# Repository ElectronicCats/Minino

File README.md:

# Minino

<p align="center">
    
</p>

<p align=center>

</p>

Minino is an original multiprotocol and multiband board made for sniffing, communicating, and attacking IoT (Internet of Things) devices. It was designed as a mini Cat that integrates the powerful ESP32-C6, GPS, microSD card slot, and OLED display. This board is a mini Swiss army knife for IoT security researchers, developers, and enthusiasts. 

Minino can operate across multiple wireless technologies and RF tools:
- **BLE** (Trackers scanner for AirTag, SmartTag, Tile, Chipolo & BLE Spam / HID)
- **Wi-Fi** (Sniffer, Deauthenticator, CatDoS, SSID Spam, Captive Portal, DroneID)
- **RF Spectrum Analyzer** (2.4 GHz Wi-Fi & Zigbee real-time analyzer, Fox Hunting, Peak Tracker, Jammer & DroneID IDS, PCAP capture)
- **Software Defined Radio (SDR)** (Native 80 MS/s I/Q transceiver, CW/Packet TX, On-Chip FFT, and [ESPARGOS WebSDR](https://espargos.net/espsdr/app/) Host)
- **Surveillance Detection** (Flock Safety ALPR, Body Cams, Skimmers)
- **Zigbee** (IEEE 802.15.4 Sniffer over CLI and Spoofing)
- **Thread & Matter** (IEEE 802.15.4 / 6LoWPAN Sniffer and Broadcast)
- **GPS** (Wardriving & Geotagged Evidence Logging)

## Features
- Compatible with CatSniffer's PyCatSniffer
- Compatible with Wireshark (Live serial streaming & `.pcap` logging on microSD)
- Compatible with [ESPARGOS WebSDR](https://espargos.net/espsdr/app/) (Browser-based real-time waterfall, FFT spectrum, and I/Q capture over WebSerial)
- Real-time 2.4 GHz RF Spectrum Analyzer with Fox Hunting, 2X Peak Tracker, EMA filtering, and Smart Anti-Jammer detection
- Selectable OLED Menu Styles (`Classic`, `Icon List`, `Grid`, `Hero + Dock`)
- WarDriving (WiFi, Zigbee, Thread, BLE, Surveillance)
- Multiprotocol packet sniffing
- Supports `.pcap` and `.iq` file storage on microSD
- File Manager Web & Local OLED Browser
- Unified firmware image generation (`minino-merged.bin` and `minino-merged.hex`)
- OpenSource & Open Hardware
- OTA Updates

### TODO Features

`[] Features coming soon [x] Working features`

>[!IMPORTANT]
> OTA requires 8MB. If you want to build for other memory capacities, compile without OTA.

### Menu: Applications (`Applications`)

#### WiFi (`Applications > WiFi`)
- [x] **Wardriving**: Geotagged WiFi AP discovery with GPS coordinates.
- [x] **WiFi Sniffer / Analyzer**: Real-time 2.4 GHz channel traffic monitoring and AP summary.
- [x] **WiFi Deauther**: Injects 802.11 deauthentication frames to disconnect target devices.
- [x] **Deauth Scan (Detector)**: Continuously monitors the airwaves for active deauth attacks.
- [x] **DOS Attack (CatDoS)**: Wireless Denial of Service and beacon flooding.
- [x] **SSID Spammer**: Broadcasts thousands of fake WiFi Access Points simultaneously.
- [x] **Captive Portal**: Rogue AP with captive portal web server for testing.
- [x] **DroneID Scanner**: Listens for and decodes ASTM F3411 Remote ID drone telemetry and GPS location.
- [x] **DroneID Transmitter**: Broadcasts simulated Drone Remote ID beacons.
- [x] **Modbus TCP**: Industrial IoT and SCADA Modbus TCP endpoint scanner.
- [x] **Flock / ALPR Detector**: Detects Flock Safety ALPR cameras, body cams, and skimmers.
- [x] **Flock Simulator**: Transmits test surveillance telemetry beacons for detection auditing.
- [ ] Wireshark integration

#### BLE (`Applications > Bluetooth`)
- [x] **BLE Spammer**: Floods advertisement popups targeting iOS (Apple), Android, Windows, and Samsung devices.
- [x] **BLE Saturate**: Lab-only channel-saturation mode with 20 ms advertising and MAC rotation.
- [x] **BLE Matter Spoof**: Emits Matter commissioning onboarding advertisements (`0xFFF6`).
- [x] **BLE HID Spoofing**: Emulates Bluetooth Human Interface Devices (keyboard, mouse, media remote).
- [x] **BLE ADV Sniffer**: Raw advertisement packet sniffer with Wireshark serial streaming.
- [x] **BLE Trackers Scanner**: Detects and tracks Apple AirTags, Samsung SmartTags, Tile, and Chipolo with RSSI signal and distance estimation.
- [x] **Wireshark integration**: Real-time BLE packet capture over serial.

#### Zigbee (`Applications > Zigbee`)
- [x] **Zigbee Sniffer**: IEEE 802.15.4 over-the-air packet sniffer.
- [x] **Zigbee Spoofing**: End Device emulation (smart light bulbs and switches).
- [x] **Mesh Topology**: Passive PAN/link map with LQI/RSSI and SD logging.
- [x] **Wardriving (WarBee)**: Geotagged Zigbee network reconnaissance with channel hopping.
- [x] **Wireshark integration**: Zigbee frame capture streaming to Wireshark.

#### Thread (`Applications > Thread`)
- [x] **Thread Sniffer**: IEEE 802.15.4 / 6LoWPAN Thread network packet sniffer.
- [x] **Thread Broadcast**: Injects multicast and broadcast packets into Thread networks.
- [x] **Wardriving (WarThread)**: Geotagged Thread/802.15.4 reconnaissance with MLE parsing.
- [x] Wireshark integration

#### Matter (`Applications > Matter`)
- [x] **Matter onboarding advertisement spoofing (BLE)**: `Applications > Bluetooth > Spam > Matter`.
- [ ] Matter protocol support
- [ ] Matter CLI

#### GPS (`Applications > GPS`)
- [x] **Wardriving**: Geotagged reconnaissance (WiFi, Zigbee, Thread) logged to SD card.
- [x] **Location**: Displays real-time latitude, longitude, and altitude coordinates.
- [x] **Speed**: Displays GPS ground speed (km/h) and heading direction.
- [x] **Date & Time**: Atomic clock synchronization and RTC update.
- [x] **Route**: Route and waypoint recording to SD card (.gpx / .csv).
- [x] **Num Sats**: Displays active satellite constellation and SNR signal quality.
- [ ] GPS Sleep

#### GPIO (`Applications > GPIO`)
- [x] **I2C Scanner**: Scans external I2C bus (SDA/SCL) device addresses.
- [x] **UART Bridge**: Hardware serial bridge / pass-through console on UART2.

#### File Manager (`Applications > File Manager`)
- [x] **File Manager Local**: On-device microSD file browser using OLED screen and buttons.
- [x] **File Manager Web**: Embedded HTTP web server for WiFi-based file downloads and uploads.

#### Spectrum (`Applications > Spectrum`)
- [x] **14-Channel Bars (`BARS`)**: Real-time 2.4 GHz bar chart overview with Peak Hold markers across all channels.
- [x] **Live Channel Scope (`SCOPE`)**: Single-channel rolling time-domain power curve and RSSI telemetry.
- [x] **2D Waterfall (`WATER`)**: Rolling spectrogram for visualizing transient transmissions and duty cycles.
- [x] **Fox Hunting Meter (`FOX`)**: High-contrast direction-finding proximity gauge (`0-100%`), calibrated dBm scale (`-90` to `-30 dBm`), Peak Hold line, and Squelch threshold marker.
- [x] **2X Peak Tracker (`PEAK`)**: Big-font display highlighting the strongest active signal (`dBm`), channel number, and center frequency (`MHz`) for rapid field readings.
- [x] **Dual-Band & Tri-Channel Sweep**: Supports both **Wi-Fi** (`Ch 1-14`, `2412-2484 MHz`) and **IEEE 802.15.4 / Zigbee** (`Ch 11-26`, `2405-2480 MHz`), plus rapid **Tri-Channel Sweep** (`Ch 1, 6, 11`).
- [x] **Smart Anti-Jammer & RF IDS**: Multi-factor evaluator (`rf_jammer_evaluate`) and EMA filter (`rf_filter_ema_rssi`) that distinguish Layer-1 RF noise/CW jammers and Layer-2 Deauth floods (`0xC0`/`0xA0`) from normal high-throughput AP traffic and adjacent-channel spillover.
- [x] **Passive DroneID Detection**: Inspects ASTM F3411 (`OUI FA:0B:BC`), French Direct Remote ID (`OUI 6A:5C:35`), and Wi-Fi Aware NAN (`88:69:19:9D:92:09`) frames to alert and log active drone UAS IDs per channel.
- [x] **Direct PCAP & CSV Logging**: Streams raw 802.11 frames to microSD (`/sdcard/spectrum_XX.pcap`) and signal telemetry to CSV without dropping the spectrum view.

#### SDR (`Applications > SDR`)
- [x] **RX I/Q Burst Capture (`[IDL]` / `[RX]`)**: Native in-process 80 MS/s hardware DMA/dump capture into reserved SRAM (`0x40840000`), live physical RSSI calculation (`dBm`), and automatic `.iq` file saving to microSD (`/sdcard/sdrcapXX.iq`).
- [x] **802.11 Raw Packet TX (`[TX:PKT]`)**: Injects bursts of custom 802.11 raw Probe Request frames (`MININO-SDR-TX`) on the selected channel (`2412-2484 MHz`, `Ch 1-14`).
- [x] **PHY Continuous Wave Carrier (`[TX:CW]`)**: Emits an unmodulated RF test carrier on the tuned frequency via the ESP32-C6 PHY synthesizer with a 30-second hardware safety timeout.
- [x] **ESPARGOS WebSDR Host (`[HOST]`)**: Streams real-time I/Q bursts (`CAP16`/`CAP20` at `80`, `40`, or `16 MS/s` with software decimation and LNA gain control `0-60 dB`) and on-chip radix-2 FFT spectrum frames (`SPEC` / `SPC1`) over USB directly to the **[ESPARGOS WebSDR App (`https://espargos.net/espsdr/app/`)](https://espargos.net/espsdr/app/)**.

---

### Menu: Settings (`Settings`)
- [x] **Display**: Configures OLED screensaver style and timeout.
- [x] **Menu Style**: Selectable OLED menu rendering views persisted in NVS (**Classic**, **Icon List**, **Grid**, and **Hero + Dock**).
- [x] **Logs Output**: Configures serial and on-screen log levels.
- [x] **SD Card Settings**: Displays SD capacity, checks format integrity, and provides FAT32 formatting.
- [x] **WiFi Settings**: Manages WiFi station credentials and radio settings.
- [x] **Stealth Mode**: Disables all LEDs, buzzer sounds, and screen animations for silent operation.
- [x] **Light Sleep Mode**: Low-power sleep mode for battery saving.
- [ ] Deep Sleep Mode

---

### Menu: About (`About`)
- [x] **Version & License**: Displays firmware version, build date, and licensing details.
- [x] **Credits & Legal**: Contributor credits and responsible disclosure notice.
- [x] **OTA Firmware Update**: Over-The-Air firmware updates via WiFi.

---

## Firmware profiles and memory budget

The default firmware includes the **Zigbee/OpenThread stacks**, so their apps
are native entries in `Applications`:

```bash
cd firmware
make compile                 # default: BLE/WiFi + Zigbee/Thread
make build-sdr               # SDR capture bank, Zigbee/Thread off
```

The SDR variant turns the stacks off because the capture bank needs the SRAM.
In the default combined build, `bt_spam` starts with roughly 20 KB free after
Bluedroid comes up and refuses to advertise below **18 KB**; it stops the loop
below **8 KB**. This prevents `btm_ble_write_adv_enable_complete failed` after
using Thread Sniffer/Broadcast, when the heap is lower.

---

## Native 80 MS/s SDR Transceiver & ESPARGOS WebSDR Host

Minino integrates a **native, in-process Software Defined Radio (SDR)** engine (`firmware/main/modules/esp_sdr/`) running directly inside Minino OS without requiring dual-boot or a secondary `ota_1` partition. It drives the ESP32-C6 hardware I/Q dump engine at **80 MS/s**, reserves the 128 KiB SRAM Block 2 (`0x40840000 - 0x40860000`) at link time (`esp_sdr_bank.ld`), and locks the USB-Serial-JTAG reset register (`usb_uart_chip_rst_dis = 1`) while active so browser WebSerial DTR/RTS transitions never reboot the board.

### Building & Flashing the SDR Firmware Variant
Because the hardware I/Q capture bank requires 128 KiB of contiguous SRAM below `0x40840000`, the SDR variant compiles without the Zigbee and OpenThread stacks to fit within the 256 KiB lower-SRAM budget (`profiles/sdr/profile`). Every build automatically generates both individual partition binaries and unified single-file images (`minino-merged.bin` and `minino-merged.hex`):

```bash
cd firmware
make build-sdr                                    # Builds the SDR-enabled firmware in build-sdr/
idf.py -B build-sdr -p /dev/ttyACM0 flash         # Flashes bootloader, partition table, and app
```

Or flash the single unified binary at address `0x0`:
```bash
esptool.py --chip esp32c6 -p /dev/ttyACM0 write_flash 0x0 build-sdr/minino-merged.bin
```

### The 4 Operating Modes on Device (`Applications > SDR`)
Inside `Applications > SDR` (or by running `sdr_capture` in the serial console), press **`BOOT`** or **hold `RIGHT`** to cycle through the four operating modes:

| Mode Header | Function | Controls |
| :--- | :--- | :--- |
| **`MININO SDR [IDL]` / `[RX]`** | **RX I/Q Burst Capture**: Captures 8,192 32-bit I/Q words (`10-bit signed I` in bits `9:0`, `10-bit signed Q` in bits `19:10`) at 80 MS/s, computes physical RSSI (`dBm`), and saves `/sdcard/sdrcapXX.iq`. | `UP`/`DOWN`: Tune `2412-2484 MHz` (`Ch 1-14`)<br>`RIGHT`: Capture & Save<br>`BOOT` / `Hold RIGHT`: Next mode<br>`LEFT`: Exit |
| **`MININO SDR [TX:PKT]`** | **802.11 Raw Packet Injection**: Transmits 5-packet bursts of raw 802.11 Probe Request frames (`SSID: MININO-SDR-TX`) on the active channel. | `UP`/`DOWN`: Tune channel<br>`RIGHT`: Send packet burst<br>`BOOT` / `Hold RIGHT`: Next mode |
| **`MININO SDR [TX:CW]`** | **PHY Continuous Wave Tone**: Emits an unmodulated RF carrier via the ESP32-C6 PHY synthesizer (`c6_sdr_tx_carrier_start`) with an automatic **30-second safety timeout**. | `UP`/`DOWN`: Tune channel<br>`RIGHT`: Toggle CW ON/OFF<br>`BOOT` / `Hold RIGHT`: Next mode |
| **`MININO SDR [HOST]`** | **ESPARGOS WebSDR Host**: Serves the ESP-SDR line/binary protocol over USB for real-time waterfall, FFT, and I/Q streaming in the browser. | `BOOT`: Exit Host mode to RX<br>`LEFT`: Stop Host & Exit app |

### Using the SDR Host with the ESPARGOS WebSDR Page
Minino is fully compatible with the official **[ESPARGOS WebSDR application (`https://espargos.net/espsdr/app/`)](https://espargos.net/espsdr/app/)**, providing a real-time waterfall, spectrum analyzer, constellation viewer, and I/Q burst streamer in any Chromium-based browser (Chrome, Edge, Brave) via WebSerial:

1. **Connect Minino via USB** and open `Applications > SDR` on the device.
2. **Open [https://espargos.net/espsdr/app/](https://espargos.net/espsdr/app/)** in your browser and click **Connect** to select the Minino USB serial port (`/dev/ttyACM0` or `COMx`).
3. **Automatic & Manual Activation**:
   - **Auto-Switch from SDR App**: If you are anywhere inside `Applications > SDR`, as soon as the ESPARGOS web app sends its initial `SYNC` handshake, Minino **automatically switches into `[HOST]` mode**, suspends the interactive serial console, and begins streaming.
   - **Manual Toggle on OLED**: Press `BOOT` (or hold `RIGHT`) inside the SDR app until the screen displays `MININO SDR [HOST]` (`Web: espargos.net` / `App: /espsdr/app`), then click **Connect** on the web page.
   - **From Serial Console**: Type `sdr_host` in the Minino console (`115200` baud) to hand over the USB port directly.
4. **Supported ESPARGOS WebSDR Capabilities**:
   - **On-Chip Spectrum (`SPEC` / `SPC1`)**: High-FPS radix-2 Q15 FFT computed directly on the ESP32-C6 (`256`, `512`, `1024`, or `2048` bins) with DC offset modes (`DC 0`/`DC 1`) and zlib CRC32 verification.
   - **Raw I/Q Burst Streaming (`CAP16` / `CAP20`)**: 8-bit (`CAP16`) and 10-bit packed (`CAP20`) I/Q transfers with hardware-chunked 64-byte USB FIFO writes.
   - **Live Parameter Negotiation**: Supports on-the-fly center frequency tuning (`FREQ 2412..2484`), sample rate decimation (`80 MS/s`, `40 MS/s`, `16 MS/s`), and RX LNA gain control (`GAIN 0..60 dB`).
5. **Exiting Host Mode**: Disconnect from the browser (sends `RELEASE`), press `LEFT` or `BOOT` on Minino, or send `MININO\n` over serial. *(Note: Do not click "Flash Firmware..." on the ESPARGOS page, as that overwrites Minino OS with upstream esp-sdr).*

---

## RF Spectrum Analyzer & Fox Hunting

The **RF Spectrum Analyzer** (`Applications > Spectrum`, implemented in `firmware/main/apps/rf_spectrum/`) operates directly on the ESP32-C6 physical (PHY) and MAC layers to provide real-time 2.4 GHz situational awareness and transmitter hunting:

- **5 Interactive OLED Views** (cycle with `RIGHT`):
  1. **`BARS`**: 14-channel bar chart with Peak Hold indicators.
  2. **`SCOPE`**: Single-channel real-time RSSI oscilloscope trace.
  3. **`WATER`**: 2D rolling waterfall spectrogram.
  4. **`FOX` (Fox Hunting)**: High-contrast direction-finding proximity meter (`0-100%`) with calibrated dBm ticks (`-90` to `-30 dBm`), Peak Hold line (`|`), Squelch marker (`:`), and Geiger counter audio clicks (`HOLD UP`).
  5. **`PEAK` (2X Peak Tracker)**: Large 2X-scaled readout of the strongest detected signal (`dBm`), channel, and frequency (`MHz`).
- **Signal Processing & Smart Anti-Jammer**:
  - **EMA Smoothing**: Applies an Exponential Moving Average filter (`rf_filter_ema_rssi`) to stabilize noisy RSSI readings while preserving rapid peak attack.
  - **Intelligent Jammer Evaluator (`rf_jammer_evaluate`)**: Cross-checks RSSI saturation (`>= -45 dBm`), valid 802.11 frame counts, beacon presence, FCS CRC error ratios, Deauth/Disassoc counts (`0xC0`/`0xA0`), and adjacent-channel AP spillover (`+-1` channel at `>= -38 dBm`) to eliminate false positives from nearby routers.
- **Passive DroneID & PCAP Forensics**:
  - Automatically decodes ASTM F3411 / ASD-STAN (`FA:0B:BC`), French Direct Remote ID (`6A:5C:35`), and Wi-Fi Aware NAN (`88:69:19:9D:92:09`) beacons, displaying `! DRONE CH X !` and logging the drone's serial `UAS ID`.
  - Hold `DOWN` (or run `spectrum_pcap on`) to stream raw 802.11 frames into sequential `/sdcard/spectrum_00.pcap` files compatible with Wireshark.
- **Serial Console Commands**: Control and inspect live state via `spectrum_pcap [on|off|toggle]`, `spectrum_drone [clear]`, `spectrum_ids [clear]`, `threshold [<dBm>|off]`, `spectrum_audio [on|off|toggle]`, `spectrum_band [wifi|zigbee]`, and `exit_app`.

---

## Core Architecture & Resource Arbitration

Minino OS uses a deterministic resource management and lifecycle architecture across all wireless modules:
- **`radio_lease` (`components/radio_lease/`)**: Reference-counted hardware arbiter that manages mutually exclusive Wi-Fi/802.15.4 and BLE radio claims plus shared promiscuous RX leases (`RADIO_PROM_SDR_RX`, `RADIO_PROM_SPECTRUM`, `RADIO_PROM_SURV`, `RADIO_PROM_ANALYZER`).
- **`wifi_service` (`components/wifi_service/`)**: Centralizes `esp_wifi_init()` and netif creation so switching between AP, STA, Sniffer, Spammer, and SDR modes never triggers duplicate netif assertions or memory leaks.
- **`gap_dispatcher` & `gatt_dispatcher` (`components/gap_dispatcher/`)**: Multiplexes Bluedroid GAP and GATTC callbacks to multiple concurrent subscribers without callback rotation conflicts.
- **`app_manager` & Selectable OLED Menu Styles (`main/modules/menus_module/`)**: Clean `minino_app_t` (`on_enter`, `on_input`, `on_exit`) lifecycle with a dedicated FreeRTOS button input queue and four NVS-persisted UI styles (`Classic`, `Icon List`, `Grid`, `Hero + Dock`).
- **Host Unit Test Suite**: Over 20 host-side Unity and Python test suites (`make -C firmware tests`) validating protocol parsers, FFT math, channel clamping, radio leases, and NMEA/PCAP formatting on standard `gcc` without hardware.

---

## BLE Trackers Scanner
Minino includes a dedicated scanner and tracker for Bluetooth Low Energy beacon devices:
- **Supported Ecosystems**: Apple Find My / AirTags, Samsung Galaxy SmartTag / SmartTag2, Tile (Mate, Pro, Slim), and Chipolo.
- **Proximity & Signal Monitoring**: Real-time RSSI signal tracking, proximity approximation, and packet reception rates.
- **Detailed Inspection**: Live viewing of device MAC address, manufacturer payload, registered status, and last-seen timestamps.
- **Paging & Filtering**: Navigate easily across multiple active trackers in range.

## Surveillance & Flock Safety Detector
Minino features an advanced passive detection engine designed to detect physical surveillance infrastructure in real time:
- **Flock Safety / ALPR Detection**: Detects Automated License Plate Readers (ALPR) such as Flock Safety cameras, Falcon systems, and Raven audio detection units.
- **Multi-Vector Fingerprinting**:
  - **WiFi**: Matches known OUI vendor prefixes (35+ Flock OUIs, DeFlock database), surveillance SSIDs (`flocksafety`, `pigvision`, `fs ext`, `penguin`, etc.), and 802.11 Information Element (IE) signatures.
  - **BLE**: Identifies characteristic advertising beacons and vendor payloads (e.g. Xuntong BLE modules, Flock battery diagnostics).
- **Body Cameras & Skimmers**: Identifies Axon Body Worn Cameras and common Bluetooth-based payment skimmers.
- **Evidence Capture & GPS**: Automatically stores detected devices with GPS coordinates (`.csv` / `.gpx`) and captures raw network traffic (`.pcap`) on the microSD card.

Inspired by projects such as [Amini Project](https://github.com/Ocelot-Offensive-Security/Arsenal) and [USBNugget](https://github.com/HakCat-Tech/USB-Nugget).

## How to build the firmware

Check the [Developer guide](./firmware/README.md) to learn how to build the firmware from scratch.

## How to contribute 

Contributions are welcome!

Please read the document [**Contribution manual**](https://github.com/ElectronicCats/electroniccats-cla/blob/main/electroniccats-contribution-manual.md) which will show you how to contribute your changes to the project.

✨ Thanks to all our [Contributors](https://github.com/ElectronicCats/Minino/graphs/contributors)! ✨

See [**_Electronic Cats CLA_**](https://github.com/ElectronicCats/electroniccats-cla/blob/main/electroniccats-cla.md) for more information.

See the [**Community code of conduct**](https://github.com/ElectronicCats/electroniccats-cla/blob/main/electroniccats-community-code-of-conduct.md) for a vision of the community we want to build and what we expect from it.

## License

Electronic Cats invests time and resources providing this open source design, please support Electronic Cats and open-source hardware by purchasing products from Electronic Cats!

Designed by Electronic Cats.

Firmware released under a GNU AGPL v3.0 license. See the LICENSE file for more information.

Hardware released under a CERN Open Hardware Licence v1.2. See the LICENSE_HARDWARE file for more information.

Electronic Cats is a registered trademark, please do not use if you sell these PCBs.

Nov 29 2022

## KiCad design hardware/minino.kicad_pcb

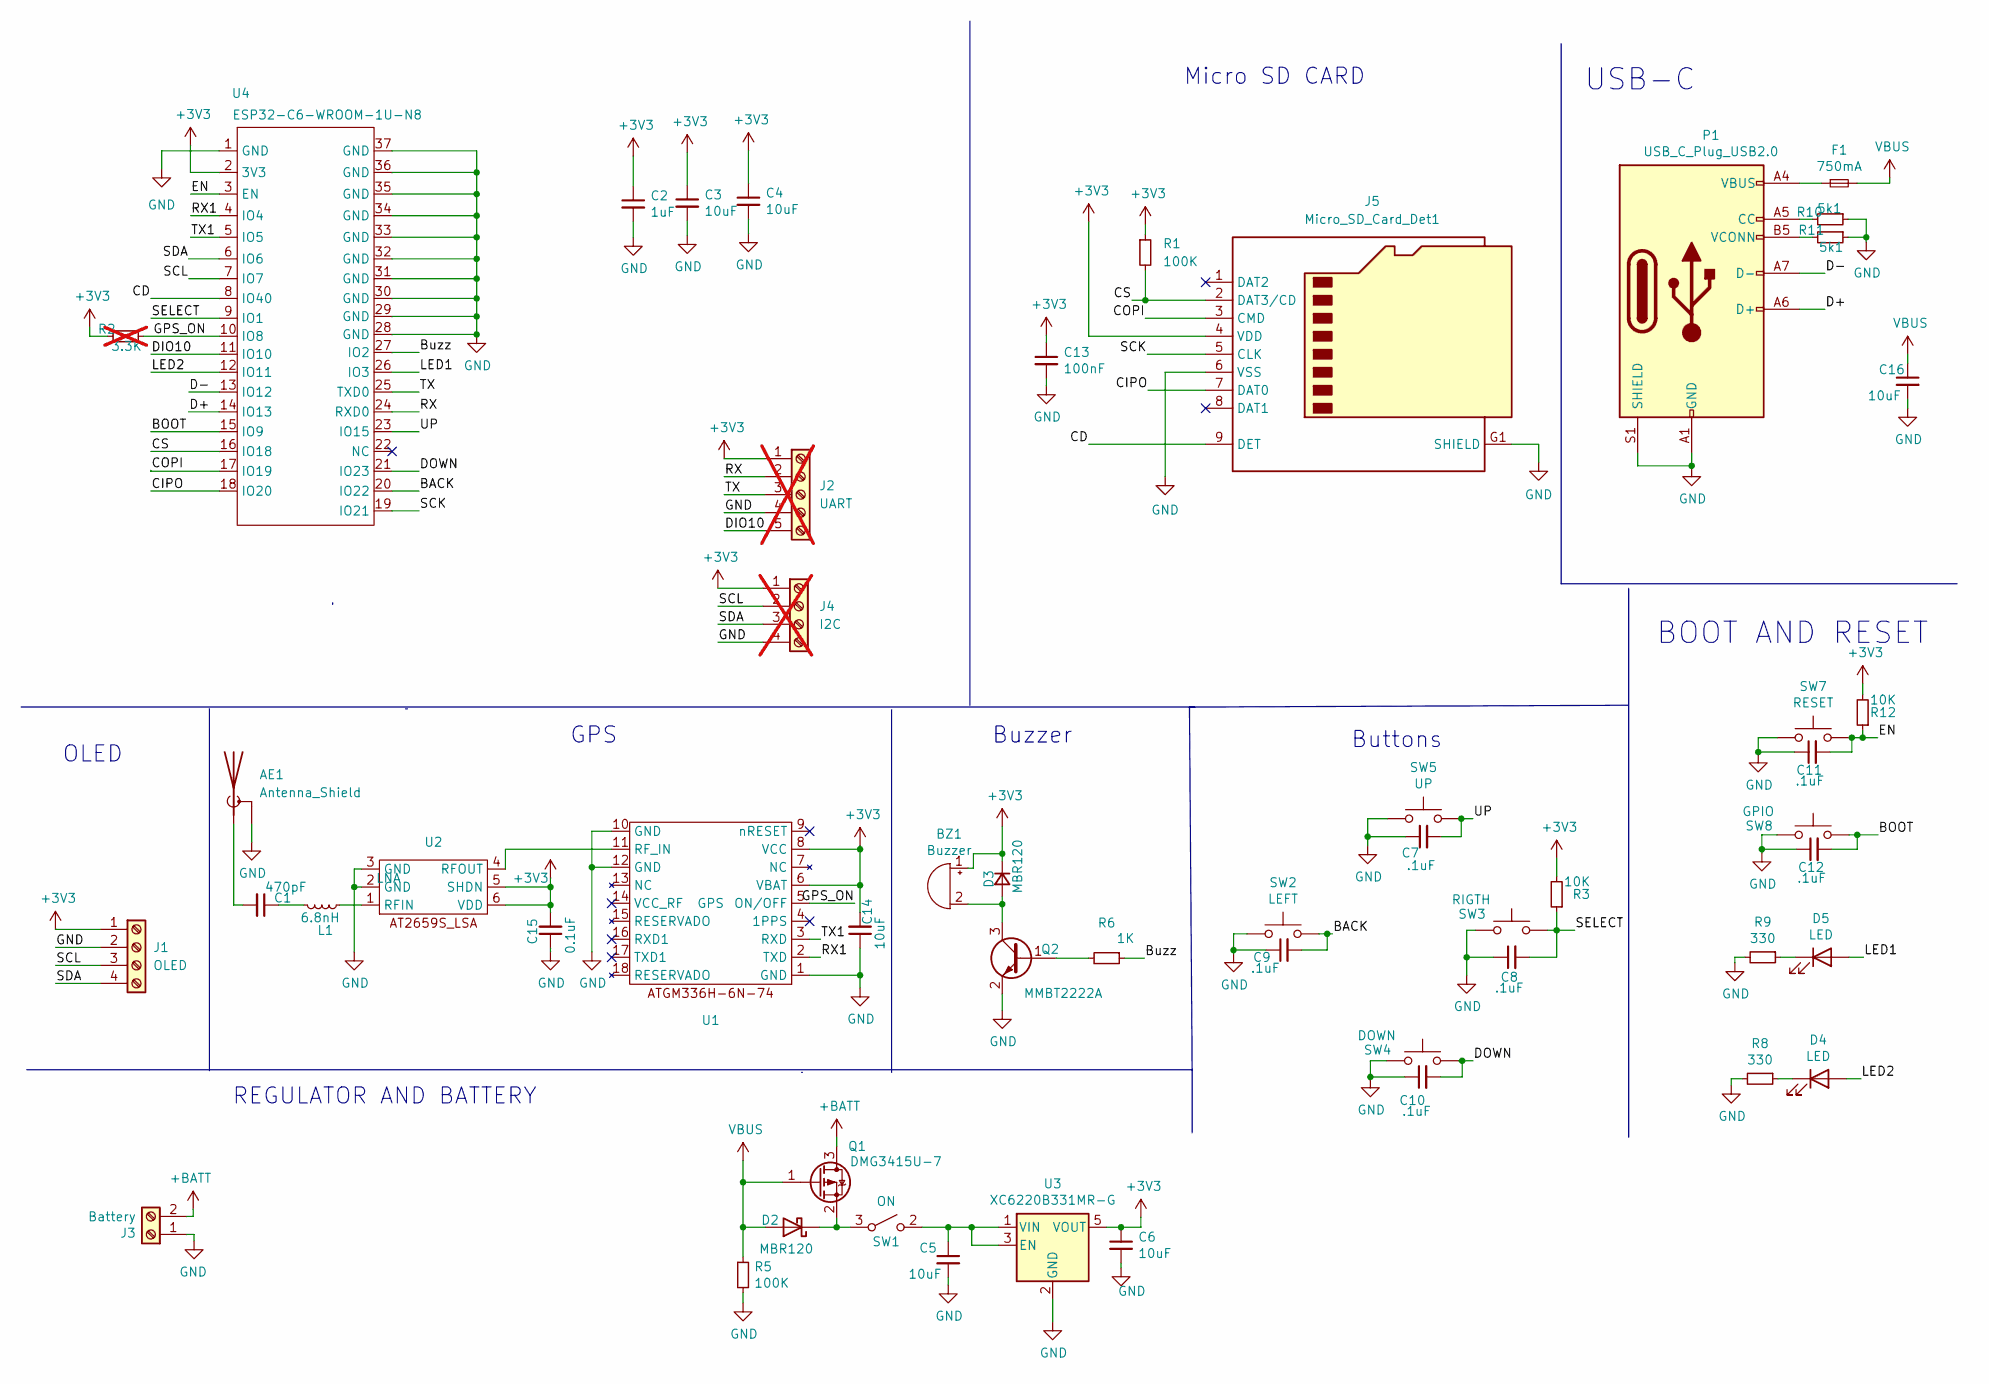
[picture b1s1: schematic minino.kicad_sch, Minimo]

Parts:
AE1: Antenna_Shield; U.FL_Molex_MCRF_73412-0110_Vertical; LCSC# C7426714
BZ1: Buzzer; Buzzer4x4; LCSC# C556936
C1: 470pF; C_0603_1608Metric; LCSC# C1620
C2: 1uF; C_0603_1608Metric; LCSC# C15849
C3, C4, C5, C6, C14, C16: 10uF; C_0603_1608Metric; LCSC# C85713
C7, C8, C9, C10, C11, C12: .1uF; C_0603_1608Metric; LCSC# C478888
C13: 100nF; C_0603_1608Metric; LCSC# C149620
C15: 0.1uF; C_0603_1608Metric; LCSC# C478888
D2, D3: MBR120; D_SOD-123F; LCSC# C130880
D4, D5: LED; LED_0805_2012Metric_Pad1.15x1.40mm_HandSolder; LCSC# C965815
F1: 750mA; Fuse_0603_1608Metric; LCSC# C182438
J1: OLED; PinHeader_1x04_P2.54mm_Vertical
J2: UART; PinHeader_1x05_P2.54mm_Vertical; LCSC# C492404; not fitted
J3: Battery; BAT-TH_BH-AAA-A1AJ024; LCSC# C5290193
J4: I2C; PinHeader_1x04_P2.54mm_Vertical; LCSC# C2691448; not fitted
J5: Micro_SD_Card_Det1; SUNTECH_ST-TF-003A; LCSC# C393941
L1: 6.8nH; L_0603_1608Metric_Pad1.05x0.95mm_HandSolder; LCSC# C49447
P1: USB_C_Plug_USB2.0; C393939; LCSC# C393939
Q1: DMG3415U-7; SOT-23; LCSC# C96616
Q2: MMBT2222A; SOT-23; LCSC# C181121
R1, R5: 100K; R_0603_1608Metric; LCSC# C25803
R2: 3.3K; R_0603_1608Metric; LCSC# C403480; not fitted
R3, R12: 10K; R_0603_1608Metric; LCSC# C217281
R6: 1K; R_0603_1608Metric_Pad0.98x0.95mm_HandSolder; LCSC# C110776
R8, R9: 330; R_0603_1608Metric; LCSC# C25231
R10, R11: 5k1; R_0603_1608Metric; LCSC# C191782
SW1: ON; JS102011SAQN; LCSC# C221660
SW2: LEFT; SW_SPST_TL3342; LCSC# C318889
SW3: RIGTH; SW_SPST_TL3342; LCSC# C318889
SW4: DOWN; SW_SPST_TL3342; LCSC# C318889
SW5: UP; SW_SPST_TL3342; LCSC# C318889
SW7: RESET; SW_SPST_TL3342; LCSC# C318889
SW8: GPIO; SW_SPST_TL3342; LCSC# C318889
U1: GPS; GPSM-SMD_ATGM336H; LCSC# C5804601
U2: LNA; AT2659S-LSA; LCSC# C883443
U3: XC6220B331MR-G; SOT-23-5; LCSC# C86534
U4: ESP32-C6-WROOM-1U-N8; MOD28_ESP32-C6-WROOM-1U_EXP

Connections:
+3V3: BZ1.1 (-), C2.1, C3.1, C4.1, C6.1, C13.1, C14.2, C15.2, D3.1 (K), J1.1, J2.1, J4.1, J5.4 (VDD), R1.1, R2.2, R3.2, R12.2, U1.6 (VBAT), U1.8 (VCC), U2.5 (SHDN), U2.6 (VDD), U3.5 (VOUT), U4.2 (3V3)
+BATT: J3.2, Q1.3 (D)
/BACK: C9.2, SW2.2, U4.20 (IO22)
/BOOT: C12.2, SW8.2, U4.15 (IO9)
/Buzz: R6.1, U4.27 (IO2)
/CD: J5.9 (DET), U4.8 (IO40)
/CIPO: J5.7 (DAT0), U4.18 (IO20)
/COPI: J5.3 (CMD), U4.17 (IO19)
/CS: J5.2 (DAT3/CD), R1.2, U4.16 (IO18)
/D+: P1.A6 (D+), U4.14 (IO13)
/D-: P1.A7 (D-), U4.13 (IO12)
/DIO10: J2.5, U4.11 (IO10)
/DOWN: C10.2, SW4.2, U4.21 (IO23)
/EN: C11.2, R12.1, SW7.2, U4.3 (EN)
/GPS_ON: R2.1, U1.5 (ON/OFF), U4.10 (IO8)
/LED1: D5.2 (A), U4.26 (IO3)
/LED2: D4.2 (A), U4.12 (IO11)
/RX: J2.2, U4.24 (RXD0)
/RX1: U1.2 (TXD), U4.4 (IO4)
/SCK: J5.5 (CLK), U4.19 (IO21)
/SCL: J1.3, J4.2, U4.7 (IO7)
/SDA: J1.4, J4.3, U4.6 (IO6)
/SELECT: C8.2, R3.1, SW3.2, U4.9 (IO1)
/TX: J2.3, U4.25 (TXD0)
/TX1: U1.3 (RXD), U4.5 (IO5)
/UP: C7.2, SW5.2, U4.23 (IO15)
GND: AE1.2 (Shield), C2.2, C3.2, C4.2, C5.2, C6.2, C7.1, C8.1, C9.1, C10.1, C11.1, C12.1, C13.2, C14.1, C15.1, C16.2, J1.2, J2.4, J3.1, J4.4, J5.6 (VSS), J5.G1 (SHIELD), J5.G2 (SHIELD), J5.G3 (SHIELD), J5.G4 (SHIELD), P1.A1 (GND), P1.A12 (GND), P1.B1 (GND), P1.B12 (GND), P1.S1 (SHIELD), Q2.2 (E), R5.2, R8.2, R9.2, R10.1, R11.1, SW2.1, SW3.1, SW4.1, SW5.1, SW7.1, SW8.1, U1.1 (GND), U1.10 (GND), U1.12 (GND), U2.2 (GND), U2.3 (GND), U3.2 (GND), U4.1 (GND), U4.28 (GND), U4.29 (GND), U4.30 (GND), U4.31 (GND), U4.32 (GND), U4.33 (GND), U4.34 (GND), U4.35 (GND), U4.36 (GND), U4.37 (GND)
unnamed: AE1.1 (A), C1.2
unnamed: BZ1.2 (+), D3.2 (A), Q2.3 (C)
unnamed: C1.1, L1.2
unnamed: D2.1 (K), Q1.2 (S), SW1.3 (A)
unnamed: D4.1 (K), R8.1
unnamed: D5.1 (K), R9.1
unnamed: F1.1, P1.A4 (VBUS), P1.A9 (VBUS), P1.B4 (VBUS), P1.B9 (VBUS)
unnamed: P1.A5 (CC), R10.2
unnamed: P1.B5 (VCONN), R11.2
unnamed: Q2.1 (B), R6.2
unnamed: C5.1, SW1.2 (B), U3.1 (VIN), U3.3 (EN)
unnamed: U1.11 (RF_IN), U2.4 (RFOUT)
unnamed: L1.1, U2.1 (RFIN)
VBUS: C16.1, D2.2 (A), F1.2, Q1.1 (G), R5.1

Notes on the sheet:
REGULATOR AND BATTERY
Buzzer
Buttons
USB-C
OLED
BOOT AND RESET
Micro SD CARD
GPS

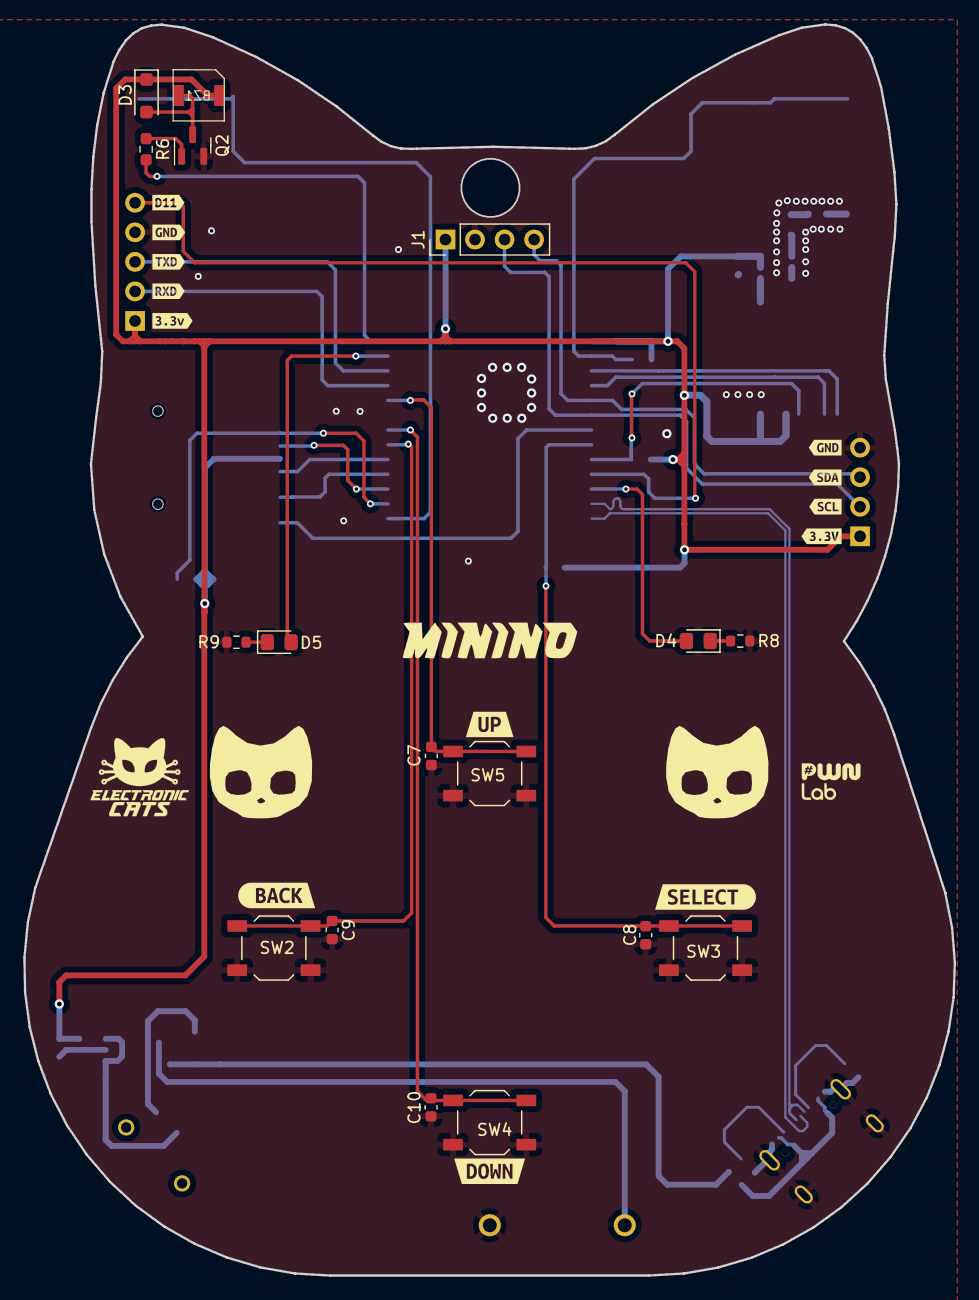
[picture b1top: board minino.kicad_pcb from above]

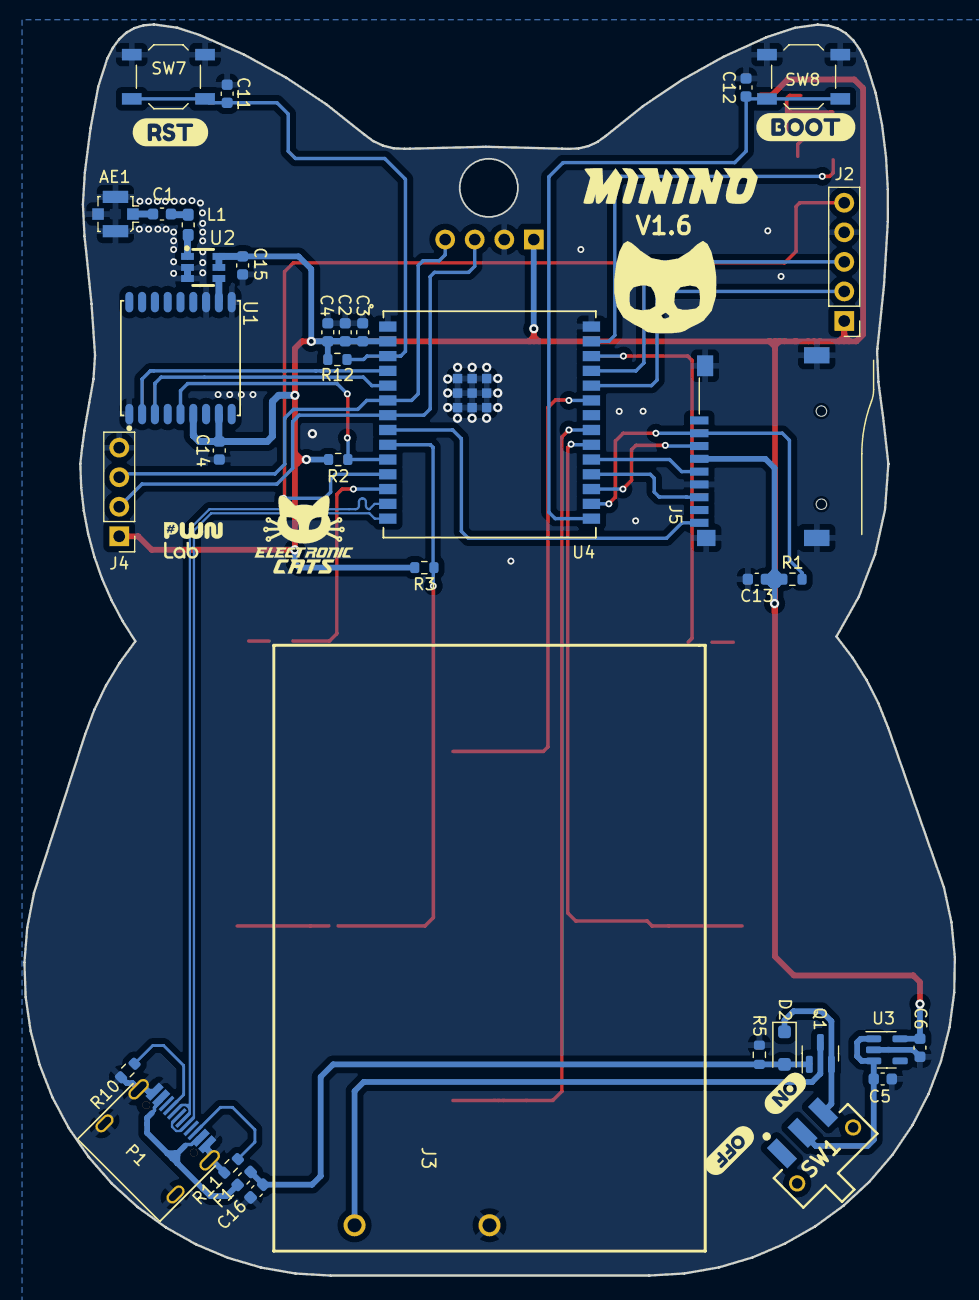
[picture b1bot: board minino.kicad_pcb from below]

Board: 2 copper layers, 80.0 x 107.5 mm, 70 parts (40 on the bottom side), 41 nets.

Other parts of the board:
kibuzzard-65BBE1AA: G***; kibuzzard-65BBE1AA
kibuzzard-65BBE1C5: G***; kibuzzard-65BBE1C5
kibuzzard-65BBE1CF: G***; kibuzzard-65BBE1CF
kibuzzard-65BBE26E: G***; kibuzzard-65BBE26E
kibuzzard-65BBE191: G***; kibuzzard-65BBE191
kibuzzard-65BBE243: G***; kibuzzard-65BBE243
kibuzzard-65BBE252: G***; kibuzzard-65BBE252
kibuzzard-65BBE261: G***; kibuzzard-65BBE261
kibuzzard-65BBE292: G***; kibuzzard-65BBE292
kibuzzard-65BC2D86: G***; kibuzzard-65BC2D86
kibuzzard-65BC2D94: G***; kibuzzard-65BC2D94
kibuzzard-65BC2DC7: G***; kibuzzard-65BC2DC7
kibuzzard-65BC2DE2: G***; kibuzzard-65BC2DE2
kibuzzard-65BC2DF2: G***; kibuzzard-65BC2DF2
kibuzzard-65BC2E00: G***; kibuzzard-65BC2E00
kibuzzard-65BC266D: G***; kibuzzard-65BC266D
kibuzzard-65BC2610: G***; kibuzzard-65BC2610

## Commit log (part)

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2025-07-17 feat(captive): Redirects user after captive portal input
    Updates the captive portal validation to redirect the user
    to the portal's root after submitting the form, instead of
    displaying a success message.
2025-07-17 feat: Enables captive portal name customization
    Adds functionality to change the captive portal's AP name via a console command.
    This allows users to easily customize the network name.
    The name is stored in preferences so it persists across reboots.
2025-07-17 feat: Sets default WiFi AP name based on MAC address
    Sets the default WiFi Access Point name to include the last two octets of the ESP32's MAC address.
    This ensures that each device has a unique default AP name, reducing potential conflicts when multiple devices are in close proximity.
    Also, frees the allocated wifi_name memory after use to prevent memory leaks when a custom SSID is used.
2025-07-19 feat: Adds captive portal redirect functionality
    Adds the functionality to redirect users to a specific HTML page after connecting to the captive portal.
    This includes:
    - Adding a new "redirect" option to the captive portal menu.
    - Implementing a new handler for the "/redirect" URI.
    - Adding functions to read and manage redirect HTML files from the SD card.
    - Including a default redirect.html file.
2025-07-21 Refactor: BLE scanner for improved reliability
    Removes the timer task and relies on the scan timeout event to restart scanning, leading to a more reliable and simplified BLE scanning process.
    The scan duration is increased to 10 minutes.
    Also improves the UART sender to correctly send BLE packets.
    The adv scanner module is refactored to use the general submenu component.
2025-07-22 Revert "Merge branch 'captive_name' into blackhat"
    This reverts commit c47cef6adce7de63d82843f710b18941fbb1167d, reversing
    changes made to d0698dae8b845eb60730b1e00f22084d949e861c.
2025-07-22 feat: Enables captive portal name customization
    Allows users to change the name of the captive portal access point via a console command.
    This feature provides greater flexibility and personalization for the captive portal setup. It stores the custom name in preferences, retrieving it during AP initialization and displaying it in notif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
    Adds validation to limit name length and avoids memory allocation issues.
2025-07-22 feat: Adds captive portal redirect functionality
    Implements a redirect feature for the captive portal, allowing users to be redirected to a specific page after submitting their credentials.
    This includes adding a new "redirect" option to the main menu, allowing the user to specify a redirect HTML file from the SD card. A default redirect page is also included. After a 5 second delay, th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
2025-07-23 fix: flush buffer to file and unmount SD if pending data exists
2025-07-23 chore: drone_id revert changes
2025-07-24 chore: remove spanish comments
2025-07-24 fix: the buttons no longer open the settings menu
2025-07-25 Implements captive portal module
    Adds a captive portal module for user authentication and redirection.
    This module:
    - Creates a WiFi access point.
    - Hosts a web server to handle user input.
    - Redirects users to a portal for authentication.
    - Allows for customization of the portal through HTML files stored on an SD card.
2025-07-29 feat: Add CTRL+C to gattcmd_scan
2025-07-29 fix: init wardriving twice causes a crash
2025-07-29 fix: Adv scanner
2025-07-29 feat: Add bt recon
2025-07-31 chore: change comments to English
2025-07-31 fix: clear OLED after transfer file
2025-08-01 Revert "Merge branch 'dev' into captive_merge"
    This reverts commit 480c3d709e6f2d69120626c801466e4139270320, reversing
    changes made to 1b3a158b90417fda2086d7c91837897cd655807d.
2025-08-01 add device name for each device to connect
2025-08-01 feat: Add workes to the be stoped with CTRL+C
2025-08-01 feat: Add mac address filter for BLE recon app
2025-08-04 fix: file manager web ok after wardriving
2025-08-05 feat: Add version to minino & add filter file to captive
2025-09-04 feat: Add UTC label to screens and test mode
2025-09-23 feat: Add delete button to file manager web
2025-09-29 feat: example new functions gps
2025-10-01 feat: Add skeleton config menu
2025-10-02 feat: Add update rate
    1 Hz
    5 Hz
    10 Hz
2025-10-02 feat: Add running animation to num sats
2025-10-08 fix: Loading animation
2025-10-09 fix: checksum validation
2025-10-14 docs: examples docs
2025-10-14 refactor: Suppresses unused result warning
2025-10-16 Fix typo in menu display name from 'Trakers' to 'Trackers'
2025-10-17 Fix typo in Bluetooth trackers menu entries
    Adding rest of Typo fixes in menus.h
2025-10-17 Fix typo in command list for cmd_control
    Fixing a missing typo in cmd_control
2025-10-22 fix: set functions as the prototype
2025-10-22 fix: set parameters for some functions
2025-10-23 fix(fw): correct assigment from wifi_scanner_get_ap on deauth module
2025-10-23 fix(fw): create protoype for callback
2025-10-23 fix(fw): set variables as only array
2025-10-23 fix(fw): set prototypes for functions in general selections
2025-10-23 fix(fw): delete the type const in drone id
2025-10-23 feat(fw): change type of variable on structs
2025-10-23 feat(fw): set variables as const char with double pointer
2025-10-23 fix(fw): set type of variable
2025-10-23 feat(fw): delete unused variable
2025-10-23 feat(fw): change type of variable
2025-10-23 fix(fw): change type of variables
2025-10-23 fix(fw): set list of strings with no const
2025-10-23 fix(fw): set param as uint8_t
2025-10-23 fix(fw): variables type definition
2025-10-23 fix(fw): change type of variable
2025-10-23 fix: functions
2025-10-23 fix: warnings
2025-10-23 feat: add task manager GPS
2025-10-23 feat: add task manager led events
2025-10-23 docs: add docs status migration
2025-10-24 docs: update TODO
2025-10-24 fix: improve concurrency safety and memory handling
2025-10-29 test(fw): add a test project
2025-11-04 test: gps test
2025-11-19 test(fw): flush pcaps into storage
2025-11-24 refactor(fw): remove folder
2025-11-24 docs(fw): add comment lines
2025-11-24 feat(fw): change gps initialization
2025-11-25 refactor(fw): remove comments
2025-11-25 feat: add files for uart-bridge app
2025-12-04 test: add functions for USB Bridge
2025-12-09 feat: add usb-uart bridge
2025-12-09 refactor: delete unnecessary files
2025-12-11 ci: add code-review-cursor workflow
2025-12-11 ci: add prompt for code review
2025-12-12 feat(fw): add chip version on sdkconfig.defaults
2025-12-12 fix: add notes for beta version
2025-12-12 fix: add condition for overflow
2025-12-15 ci: change version to compile on workflow
2025-12-15 ci: allow additional tag naming formats
2025-12-17 refactor(fw): move zigbee and thread files
2025-12-18 fix(fw): add parameters on cmd callbacks functions
2025-12-19 refactor: move relative paths
2025-12-19 fix(fw): change partameter for prototype
2025-12-26 feat(fw): minino compiles with zigbee and thread
2026-03-03 Fix(fw)
    Rellocated the Wifi Spectrum Suite
2026-03-06 Add requirements.txt for WiFiSpectrumSuite dependencies
    - Added pandas, numpy, matplotlib, seaborn, and folium to requirements.txt
2026-03-09 feat(fw): WiFiSpectrumSuite
    Adds description of this tool, requirements and a Python script.
2026-03-17 feat: add initial files for WiFi Spectrum Suite including core, utils, and visualization modules
2026-04-16 feat: update .gitignore to exclude Python cache files
2026-04-16 feat: remove unused core and utils modules, add setup.py for package management
2026-04-16 feat: implement WardrivingAnalyzer class for comprehensive wardriving data analysis
2026-04-16 feat: add output module with Rich console helpers for styled messaging
2026-04-17 feat: Updated print statements to use console output functions for better formatting and consistency. - Enhanced user feedback during CSV loading, data cleaning, and analysis processes. - Improved vi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
2026-04-17 feat: add output directory handling for generated files and enhance analysis functions
2026-04-17 feat: rename WiFi_Sprectrum_Suite.py to WiFi_Spectrum_Suite.py and moved to Legacy folder
2026-04-17 feat: add unit tests for various modules including CSV handling, validators, and wardriving analysis
2026-04-17 feat: add CSV files to .gitignore to prevent tracking of generated data
2026-04-17 feat: refactor CSV line handling with dedicated split and join functions
2026-04-17 feat: add file size validation to prevent processing oversized CSV files
2026-04-17 feat: add spoofing analysis and reporting functionality in WardrivingAnalyzer
2026-04-17 feat: add spoofing analysis tests to enhance detection capabilities in WardrivingAnalyzer
2026-04-17 fix: Translated test descriptions and assertions from Spanish to English for better readability.
    - Updated parameter names in test functions to be more descriptive and consistent.
    - Improved test function names to follow a clearer naming convention.
    - Ensured that all test cases maintain the same structure and style for uniformity.
2026-04-17 docs: update README.md for enhanced user guidance and feature clarity
2026-04-20 feat: update CLI commands and add shell completion support for wifi-spectrum
2026-04-20 fix: update completion function names for consistency in CLI script
2026-04-20 fix: update completion script to use _files for better compatibility
2026-04-20 test: add unit tests for shell completion command in test_completion.py
2026-04-20 docs: add shell tab completion section to README with installation and usage details
2026-04-20 fix: simplify header label in print_header function
2026-04-20 refactor: enhance plotting functions with consistent styling and improved aesthetics
2026-04-28 refactor(zigbee): remove unused sniffer input callback and related variables refactor(config): move GPIO_RANGE_MAX configuration to the general project menu refactor(bitmaps): clean up unused arrows 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
2026-04-28 feat(zigbee): add channel selection callbacks to zigbee module and delete hardcoded channel detection
2026-04-28 feat(zigbee): add Zigbee light functionality with display status updates and signal handling
2026-04-29 feat(radio_selector): enhance radio selection functionality and integrate with Zigbee components
2026-04-29 fix(zigbee): add delay and restart in deinitialization for Zigbee light and switch components
2026-04-29 feat(zigbee): add handling for network disconnection and update display status
2026-04-29 feat(thread_sniffer): enhance packet handling and logging in thread sniffer module
2026-04-29 feat(thread_sniffer): set channel after enabling promiscuous mode and improve log message
2026-04-29 feat(thread_sniffer): improve task handling and event logging in thread sniffer
2026-04-30 fix(menus, zigbee): correct formatting and remove redundant function call in zigbee module
2026-04-30 fix(captive_module): correct memory allocation for wifi name and paths in captive module
2026-04-30 fix(warbee_module): optimize memory allocation for CSV buffer and ensure proper cleanup
2026-04-30 fix(trackers_module): improve memory management by centralizing tracker information cleanup
2026-04-30 fix(thread_sniffer): improve memory allocation handling in pcap_start function
2026-04-30 fix(trackers_module): enhance mutex handling for tracker operations
2026-04-30 fix(animations_module, oled_screen): add error handling for mutex creation
2026-05-04 fix(thread_broadcast): add error handling for UDP message reception fix(trackers_scanner): improve task deletion and state management fix(wifi_ap_manager): enhance connection handling and preferences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
2026-05-04 fix(buzzer): add task handle cleanup in buzzer_play_for function
2026-05-04 Refactor and clean up code across multiple modules
    - Removed unused function declarations and variables in http_server, bt_gatts, bt_spam, buzzer, id_open, id_open_esp32, odrone_id, spoofer, flash_fs, ieee_sniffer, ledc_controller, nmea_parser, sd_ca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
    - Updated logging macros to use consistent naming conventions in bt_gatts.
    - Fixed type casting issues for string parameters in various modules to ensure proper handling of character pointers.
    - Improved memory management by ensuring proper allocation and deallocation of dynamic memory in menus_module and gps modules.
    - Enhanced readability by adding const qualifiers wh
2026-05-04 style: format code for improved readability across multiple files
2026-05-04 fix(animations_task): improve task cleanup and prevent deadlock during stop
2026-05-04 feat(droneid_scanner): implement packet queue and processing task for improved data handling
